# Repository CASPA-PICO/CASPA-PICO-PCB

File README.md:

# CASPA-PICO-PCB
- Ci-joint se trouve les schémas et les explications qui accompagne

<h2>Schéma électrique du PCB</h2>
- Ci-joint se trouve les schémas et les explications qui accompagne
- Sur le schéma électrique vous trouverez les différents composants
- Nous avons travaillé sur une ESP32-E DFR0654
- Pour l'ethernet le composant est un ENC28J60 HR911105A
- POLULU REG09b
- Ecran OLED 

</img>

<h2>Schéma du PCB</h2>

</img>

Pour imprimer le PCB sans effectuer de changement vous pouvez directement récupéré le dossier fichiergerberfinax

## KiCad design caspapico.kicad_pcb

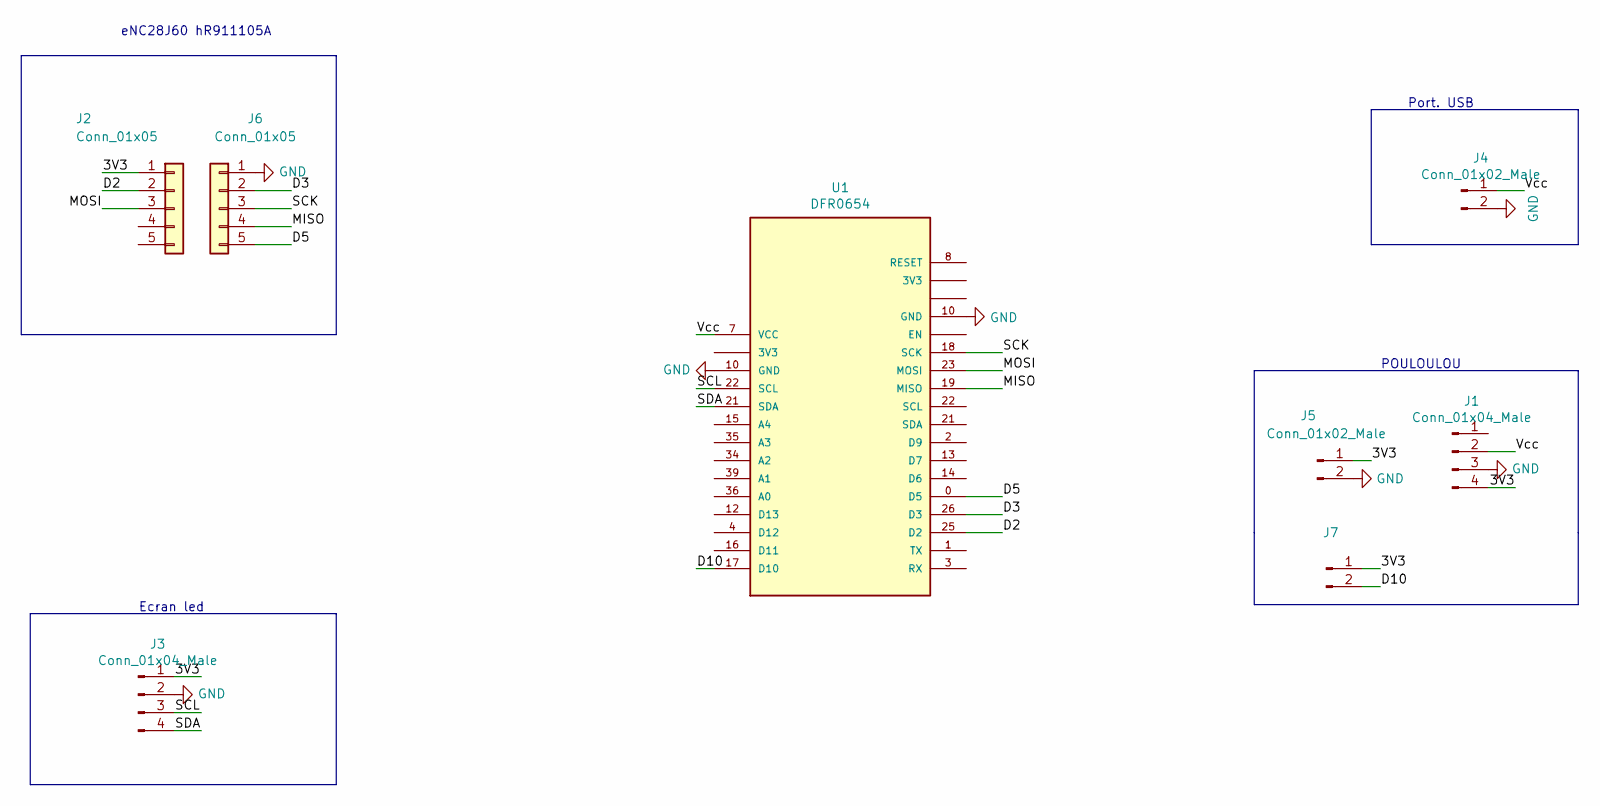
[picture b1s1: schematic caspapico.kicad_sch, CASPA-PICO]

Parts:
J1, J3: Conn_01x04_Male; PinHeader_1x04_P2.54mm_Vertical
J2, J6: Conn_01x05; PinHeader_1x05_P2.54mm_Vertical
J4, J5: Conn_01x02_Male; PinHeader_1x02_P2.54mm_Vertical
J7: (no value)
U1: DFR0654; MODULE_DFR0654

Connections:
/3V3: J1.4, J2.1, J3.1, J5.1, J7.1
/D2: J2.2, U1.25 (D2)
/D3: J6.2, U1.26 (D3)
/D5: J6.5, U1.0 (D5)
/D10: J7.2, U1.17 (D10)
/MISO: J6.4, U1.19 (MISO)
/MOSI: J2.3, U1.23 (MOSI)
/SCK: J6.3, U1.18 (SCK)
/SCL: J3.3, U1.22 (SCL)
/SDA: J3.4, U1.21 (SDA)
/Vcc: J1.2, J4.1, U1.7 (VCC)
GND: J1.3, J3.2, J4.2, J5.2, J6.1, U1.10 (GND)

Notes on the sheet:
Ecran led
Port. USB
POULOULOU
eNC28J60 hR911105A

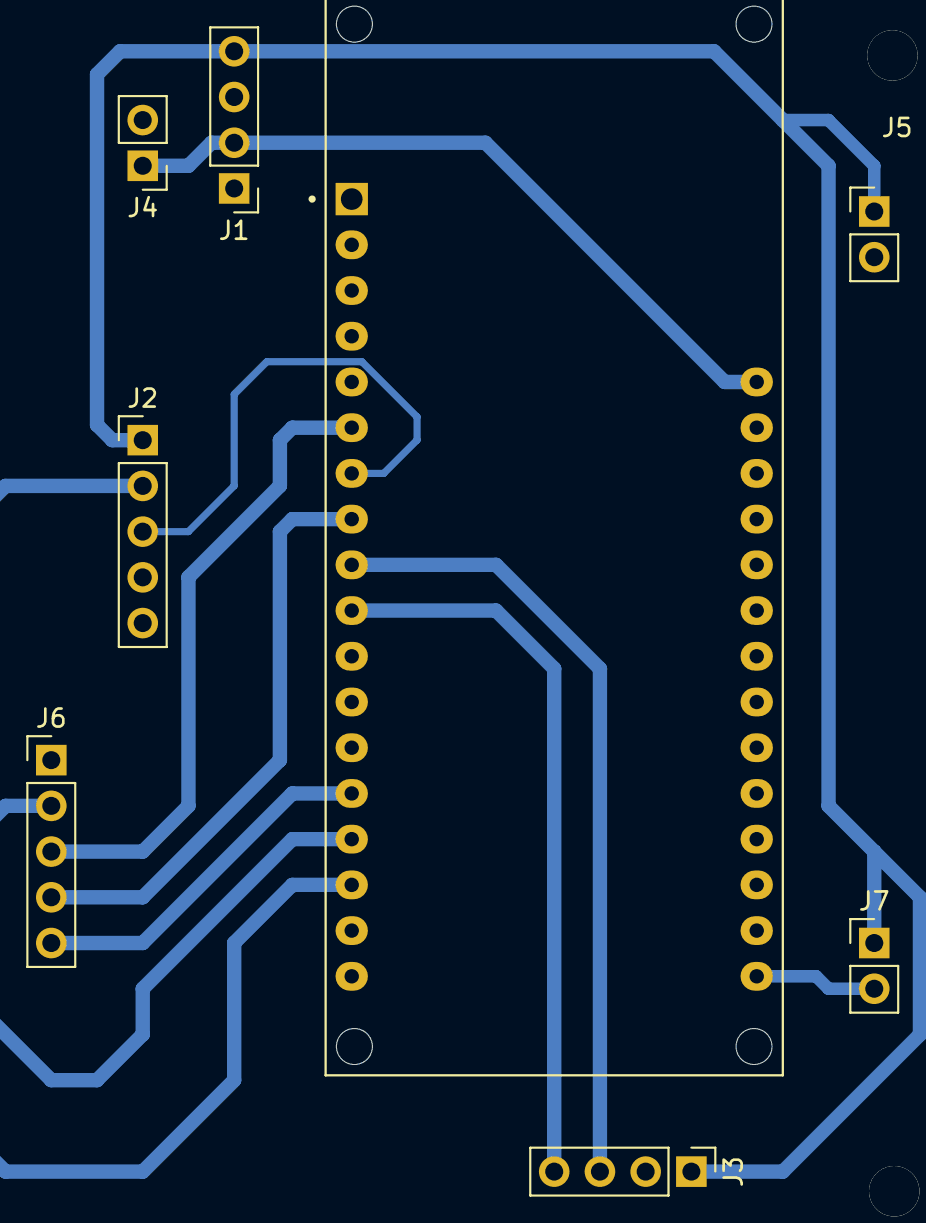
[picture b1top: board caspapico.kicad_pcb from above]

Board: 2 copper layers, 8 parts (0 on the bottom side), 12 nets.
